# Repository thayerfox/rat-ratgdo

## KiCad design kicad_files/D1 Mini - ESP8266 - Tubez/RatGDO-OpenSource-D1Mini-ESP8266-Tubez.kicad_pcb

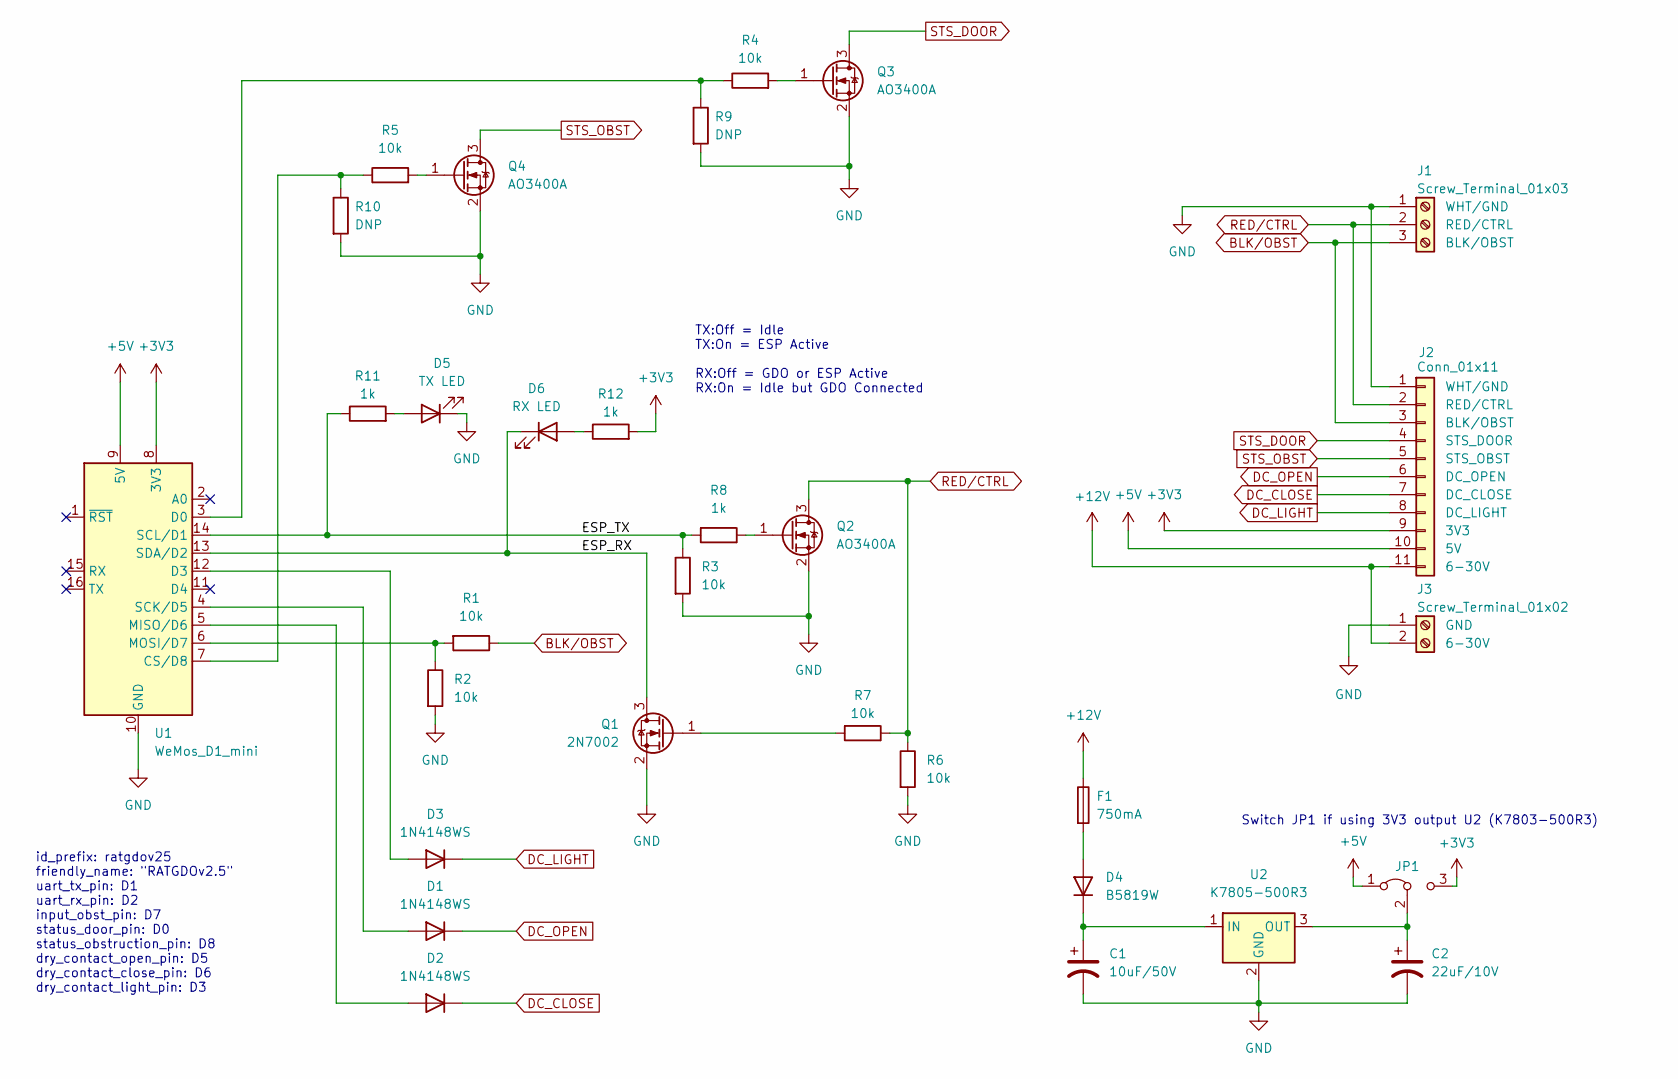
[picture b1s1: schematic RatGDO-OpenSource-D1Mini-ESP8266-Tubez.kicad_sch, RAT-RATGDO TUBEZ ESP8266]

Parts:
C1: 10uF/50V; C_0805_2012Metric_Pad1.18x1.45mm_HandSolder
C2: 22uF/10V; C_0805_2012Metric_Pad1.18x1.45mm_HandSolder
D1, D2, D3: 1N4148WS; D_SOD-323_HandSoldering
D4: B5819W; D_SOD-123
D5: TX LED; LED_0805_2012Metric_Pad1.15x1.40mm_HandSolder
D6: RX LED; LED_0805_2012Metric_Pad1.15x1.40mm_HandSolder
F1: 750mA; Fuse_1206_3216Metric_Pad1.42x1.75mm_HandSolder
J1: Screw_Terminal_01x03; TerminalBlock_Phoenix_MKDS-1,5-3_1x03_P5.00mm_Horizontal
J2: Conn_01x11; PinHeader_1x11_P2.54mm_Vertical_ExtendedPads
J3: Screw_Terminal_01x02; TerminalBlock_Phoenix_MKDS-1,5-2_1x02_P5.00mm_Horizontal
JP1: SolderJumper-3_P1.3mm_Bridged2Bar12_RoundedPad1.0x1.5mm_vol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
Q1: 2N7002; SOT-23_Handsoldering
Q2, Q3, Q4: AO3400A; SOT-23_Handsoldering
R1, R2, R3, R4, R5, R6, R7: 10k; R_0805_2012Metric_Pad1.20x1.40mm_HandSolder
R8, R11, R12: 1k; R_0805_2012Metric_Pad1.20x1.40mm_HandSolder
R9, R10: DNP; R_0805_2012Metric_Pad1.20x1.40mm_HandSolder
U1: WeMos_D1_mini; WEMOS_D1_mini_light
U2: K7805-500R3; Converter_DCDC_RECOM_R-78HB-0.5_THT_JLC_small

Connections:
+3V3: J2.9 (3V3), JP1.3 (B), R12.2, U1.8 (3V3)
+5V: J2.10 (5V), JP1.1 (A), U1.9 (5V)
+12V: F1.1, J2.11 (12V), J3.2 (6-30V)
/ESP_RX: D6.1 (K), Q1.3 (D), U1.13 (SDA/D2)
/ESP_TX: R3.1, R8.2, R11.1, U1.14 (SCL/D1)
BLK/OBST: J1.3 (BLK/OBST), J2.3 (BLK/OBST), R1.1
DC_CLOSE: D2.1 (K), J2.7 (DC_CLOSE)
DC_LIGHT: D3.1 (K), J2.8 (DC_LIGHT)
DC_OPEN: D1.1 (K), J2.6 (DC_OPEN)
GND: C1.2, C2.2, D5.1 (K), J1.1 (WHT/GND), J2.1 (WHT/GND), J3.1 (GND), Q1.2 (S), Q2.2 (S), Q3.2 (S), Q4.2 (S), R2.2, R3.2, R6.2, R9.2, R10.2, U1.10 (GND), U2.2 (GND)
unnamed: D1.2 (A), U1.4 (SCK/D5)
unnamed: D2.2 (A), U1.5 (MISO/D6)
unnamed: D3.2 (A), U1.12 (D3)
unnamed: D4.2 (A), F1.2
unnamed: C1.1, D4.1 (K), U2.1 (IN)
unnamed: D5.2 (A), R11.2
unnamed: D6.2 (A), R12.1
unnamed: C2.1, JP1.2 (C), U2.3 (OUT)
unnamed: Q1.1 (G), R7.2
unnamed: Q2.1 (G), R8.1
unnamed: Q3.1 (G), R4.2
unnamed: Q4.1 (G), R5.2
unnamed: R5.1, R10.1, U1.7 (CS/D8)
unnamed: R4.1, R9.1, U1.3 (D0)
unnamed: R1.2, R2.1, U1.6 (MOSI/D7)
RED/CTRL: J1.2 (RED/CTRL), J2.2 (RED/CTRL), Q2.3 (D), R6.1, R7.1
STS_DOOR: J2.4 (STS_DOOR), Q3.3 (D)
STS_OBST: J2.5 (STS_OBST), Q4.3 (D)

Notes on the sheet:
Switch JP1 if using 3V3 output U2 (K7803-500R3)
TX:Off = Idle TX:On = ESP Active RX:Off = GDO or ESP Active RX:On = Idle but GDO Connected
id_prefix: ratgdov25 friendly_name: "RATGDOv2.5" uart_tx_pin: D1 uart_rx_pin: D2 input_obst_pin: D7 status_door_pin: D0 status_obstruction_pin: D8 dry_contact_open_pin: D5 dry_contact_close_pin: D6 dry_contact_light_pin: D3

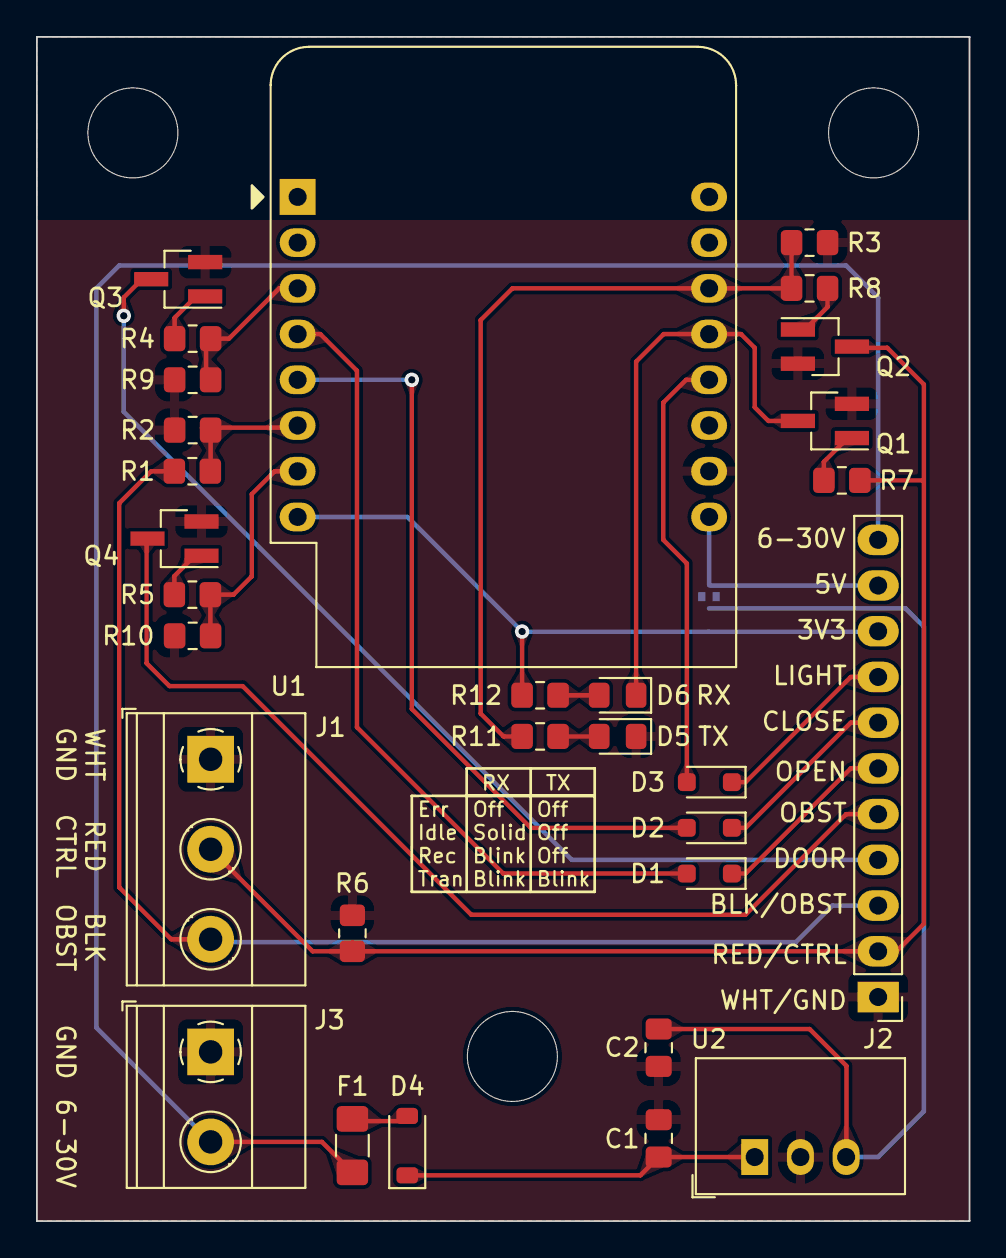
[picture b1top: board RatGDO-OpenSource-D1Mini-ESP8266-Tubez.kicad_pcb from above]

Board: 2 copper layers, 51.8 x 65.8 mm, 31 parts (1 on the bottom side), 28 nets.

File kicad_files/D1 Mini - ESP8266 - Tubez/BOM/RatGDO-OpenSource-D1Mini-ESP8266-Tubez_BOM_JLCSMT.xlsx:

Comment | Designator | Footprint | JLCPCB Part #（optional）
KF127-5.0-3P | J1 | TerminalBlock_Phoenix_MKDS-1,5-3_1x03_P5.00mm_Horizontal | C474905
10k | R3,R2,R1,R6,R7, R4, R5 | R_0805_2012Metric | C17414
AO3400A | Q3,Q4,Q2 | SOT-23_Handsoldering | C20917
1N4148WS | D1,D2,D3 | D_SOD-323_HandSoldering | C2128
2N7002 | Q1 | SOT-23_Handsoldering | C8545
KF127-5.0-2P | J3 | TerminalBlock_Phoenix_MKDS-1,5-2_1x03_P5.00mm_Horizontal | C474904
B5819W | D4 | D_SOD-123 | C8598
K7805-500R3 | U2 | Converter_DCDC_RECOM_R-78HB-0.5_THT | C909662
10uF/50V | C1 | C_0805_2012Metric_Pad1.18x1.45mm_HandSolder | C440198
22uF/10V | C2 | C_0805_2012Metric_Pad1.18x1.45mm_HandSolder | C45783
1k | R8,R11,R12 | R_0805_2012Metric | C17513
750mA | F1 | Fuse_1206_3216Metric_Pad1.42x1.75mm_HandSolder | C328915
LED Green | D5,D6 | LED_0805_2012Metric_Pad1.15x1.40mm_HandSolder | C2297
DNP-WeMos_D1_mini | U1 | WEMOS_D1_mini_light | DNP
DNP-Conn_01x11 | J2 | PinHeader_1x11_P2.54mm_Vertical | DNP
DNP | R9,R10 | R_0805_2012Metric | DNP

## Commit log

2023-11-03 add extra output/input like original ratgdo v2.5
2023-11-03 laid out pcba with new outline and keepout
2023-11-03 relayout of board
2023-11-06 dual connector
2023-11-08 Addition of 12V DC DC supply
2023-11-09 rename
2023-11-10 Change Q4 rotation 180
2023-11-10 Change angled track intersection to 90
2023-11-16 Update with potential three new v2.5 resistors.
2023-11-17 fix r3 connection wrt r8
2023-11-17 addition of LEDs
    work in progress
2023-11-18 Addition of R7/R6 and R8
2023-11-18 Missed pcb net connection to R3
2023-11-18 Move C1/C2 designators
2023-11-18 Regenerate Gerbers
2023-11-18 Added 500mA fuse to input power
    fuse is expensive on jlcpcb. need to explore other part numbers., maybe move to 1206 size ptc instead.
2023-11-21 Change to 750mA fuse 1206 package
2023-11-21 Add 750mA fuse
2023-11-21 Silkscreen change
2023-11-21 add pdf schematic
2023-11-21 Added smt pcb jumper to switch between 5V or 3v3 supply
2023-11-22 Silkscreen cleanup
2023-11-22 Add 3v3 or 5V jumper for use of different dcdc
2023-11-22 schematic note and resize of min silk text height
2023-11-22 Add LED legend and move schematic onto grid
2023-11-23 Designator notation swap
